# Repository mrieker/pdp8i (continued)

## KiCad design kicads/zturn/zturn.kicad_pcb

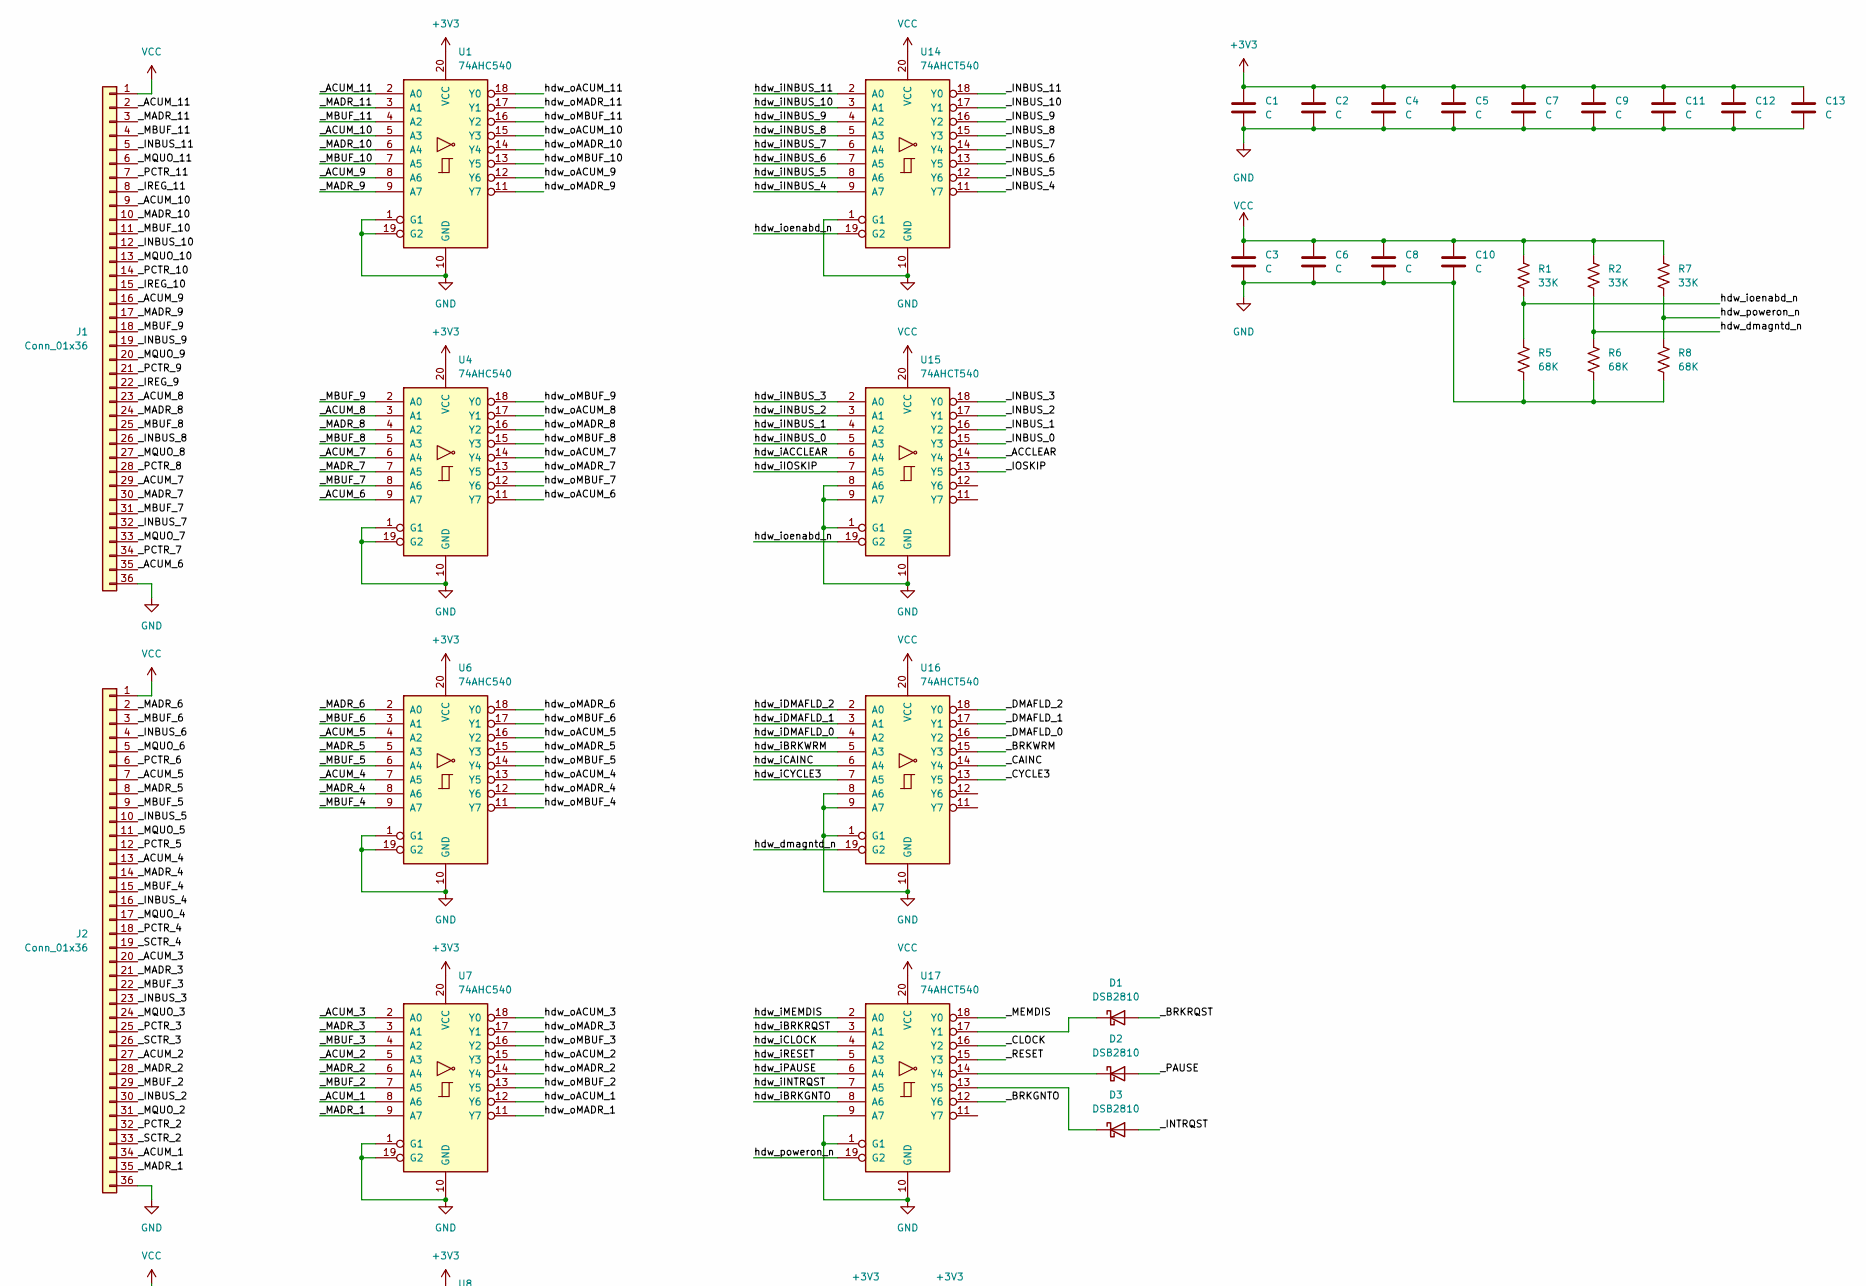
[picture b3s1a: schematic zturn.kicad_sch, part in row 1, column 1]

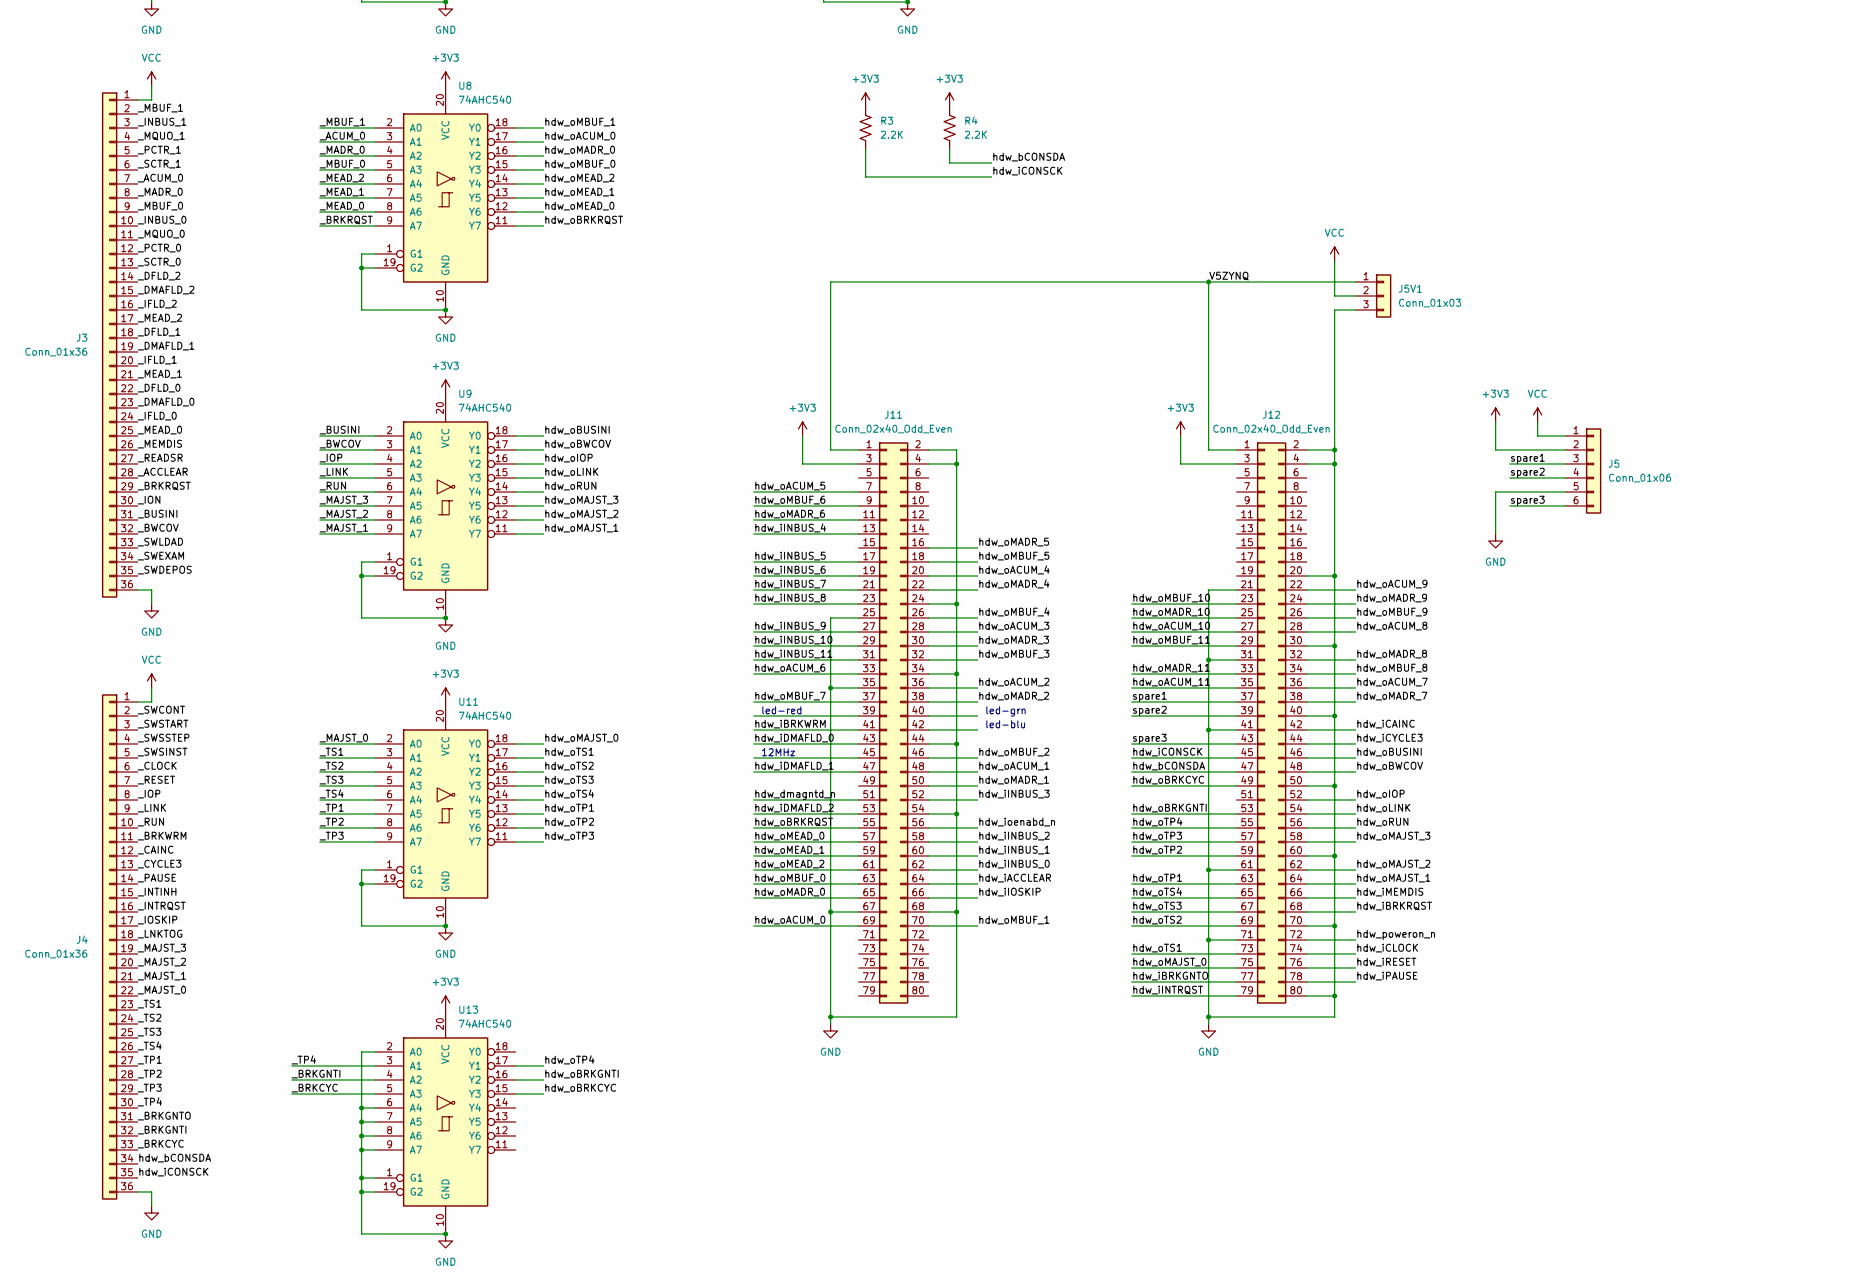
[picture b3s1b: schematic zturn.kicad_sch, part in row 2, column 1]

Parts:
C1, C2, C3, C4, C5, C6, C7, C8, C9, C10, C11, C12, C13: C; R_Axial_DIN0207_L6.3mm_D2.5mm_P7.62mm_Horizontal
D1, D2, D3: DSB2810; D_DO-35_SOD27_P7.62mm_Horizontal
J1, J2, J3, J4: Conn_01x36; PinHeader_1x36_P2.54mm_Vertical
J5: Conn_01x06; PinHeader_1x06_P2.54mm_Vertical
J5V1: Conn_01x03; PinHeader_1x03_P2.54mm_Horizontal
J11, J12: Conn_02x40_Odd_Even; PinHeader_2x40_P1.27mm_Vertical
R1, R2, R7: 33K; R_Axial_DIN0207_L6.3mm_D2.5mm_P7.62mm_Horizontal
R3, R4: 2.2K; R_Axial_DIN0207_L6.3mm_D2.5mm_P7.62mm_Horizontal
R5, R6, R8: 68K; R_Axial_DIN0207_L6.3mm_D2.5mm_P7.62mm_Horizontal
U1, U4, U6, U7, U8, U9, U11, U13: 74AHC540; DIP-20_W7.62mm
U14, U15, U16, U17: 74AHCT540; DIP-20_W7.62mm

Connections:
+3V3: C1.1, C2.1, C4.1, C5.1, C7.1, C9.1, C11.1, C12.1, C13.1, J5.2, J11.3, J12.3, R3.1, R4.1, U1.20 (VCC), U4.20 (VCC), U6.20 (VCC), U7.20 (VCC), U8.20 (VCC), U9.20 (VCC), U11.20 (VCC), U13.20 (VCC)
/V5ZYNQ: J5V1.1, J11.1, J12.1
/_ACCLEAR: J3.28, U15.14 (Y4)
/_ACUM_0: J3.7, U8.3 (A1)
/_ACUM_1: J2.34, U7.8 (A6)
/_ACUM_2: J2.27, U7.5 (A3)
/_ACUM_3: J2.20, U7.2 (A0)
/_ACUM_4: J2.13, U6.7 (A5)
/_ACUM_5: J2.7, U6.4 (A2)
/_ACUM_6: J1.35, U4.9 (A7)
/_ACUM_7: J1.29, U4.6 (A4)
/_ACUM_8: J1.23, U4.3 (A1)
/_ACUM_9: J1.16, U1.8 (A6)
/_ACUM_10: J1.9, U1.5 (A3)
/_ACUM_11: J1.2, U1.2 (A0)
/_BRKCYC: J4.33, U13.5 (A3)
/_BRKGNTI: J4.32, U13.4 (A2)
/_BRKGNTO: J4.31, U17.12 (Y6)
/_BRKRQST: D1.2 (A), J3.29, U8.9 (A7)
/_BRKWRM: J4.11, U16.15 (Y3)
/_BUSINI: J3.31, U9.2 (A0)
/_BWCOV: J3.32, U9.3 (A1)
/_CAINC: J4.12, U16.14 (Y4)
/_CLOCK: J4.6, U17.16 (Y2)
/_CYCLE3: J4.13, U16.13 (Y5)
/_DFLD_0: J3.22
/_DFLD_1: J3.18
/_DFLD_2: J3.14
/_DMAFLD_0: J3.23, U16.16 (Y2)
/_DMAFLD_1: J3.19, U16.17 (Y1)
/_DMAFLD_2: J3.15, U16.18 (Y0)
/_IFLD_0: J3.24
/_IFLD_1: J3.20
/_IFLD_2: J3.16
/_INBUS_0: J3.10, U15.15 (Y3)
/_INBUS_1: J3.3, U15.16 (Y2)
/_INBUS_2: J2.30, U15.17 (Y1)
/_INBUS_3: J2.23, U15.18 (Y0)
/_INBUS_4: J2.16, U14.11 (Y7)
/_INBUS_5: J2.10, U14.12 (Y6)
/_INBUS_6: J2.4, U14.13 (Y5)
/_INBUS_7: J1.32, U14.14 (Y4)
/_INBUS_8: J1.26, U14.15 (Y3)
/_INBUS_9: J1.19, U14.16 (Y2)
/_INBUS_10: J1.12, U14.17 (Y1)
/_INBUS_11: J1.5, U14.18 (Y0)
/_INTINH: J4.15
/_INTRQST: D3.2 (A), J4.16
/_ION: J3.30
/_IOP: J4.8, U9.4 (A2)
/_IOSKIP: J4.17, U15.13 (Y5)
/_IREG_9: J1.22
/_IREG_10: J1.15
/_IREG_11: J1.8
/_LINK: J4.9, U9.5 (A3)
/_LNKTOG: J4.18
/_MADR_0: J3.8, U8.4 (A2)
/_MADR_1: J2.35, U7.9 (A7)
/_MADR_2: J2.28, U7.6 (A4)
/_MADR_3: J2.21, U7.3 (A1)
/_MADR_4: J2.14, U6.8 (A6)
/_MADR_5: J2.8, U6.5 (A3)
/_MADR_6: J2.2, U6.2 (A0)
/_MADR_7: J1.30, U4.7 (A5)
/_MADR_8: J1.24, U4.4 (A2)
/_MADR_9: J1.17, U1.9 (A7)
/_MADR_10: J1.10, U1.6 (A4)
/_MADR_11: J1.3, U1.3 (A1)
/_MAJST_0: J4.22, U11.2 (A0)
/_MAJST_1: J4.21, U9.9 (A7)
/_MAJST_2: J4.20, U9.8 (A6)
/_MAJST_3: J4.19, U9.7 (A5)
/_MBUF_0: J3.9, U8.5 (A3)
/_MBUF_1: J3.2, U8.2 (A0)
/_MBUF_2: J2.29, U7.7 (A5)
/_MBUF_3: J2.22, U7.4 (A2)
/_MBUF_4: J2.15, U6.9 (A7)
/_MBUF_5: J2.9, U6.6 (A4)
/_MBUF_6: J2.3, U6.3 (A1)
/_MBUF_7: J1.31, U4.8 (A6)
/_MBUF_8: J1.25, U4.5 (A3)
/_MBUF_9: J1.18, U4.2 (A0)
/_MBUF_10: J1.11, U1.7 (A5)
/_MBUF_11: J1.4, U1.4 (A2)
/_MEAD_0: J3.25, U8.8 (A6)
/_MEAD_1: J3.21, U8.7 (A5)
/_MEAD_2: J3.17, U8.6 (A4)
/_MEMDIS: J3.26, U17.18 (Y0)
/_MQUO_0: J3.11
/_MQUO_1: J3.4
/_MQUO_2: J2.31
/_MQUO_3: J2.24
/_MQUO_4: J2.17
/_MQUO_5: J2.11
/_MQUO_6: J2.5
/_MQUO_7: J1.33
/_MQUO_8: J1.27
/_MQUO_9: J1.20
/_MQUO_10: J1.13
/_MQUO_11: J1.6
/_PAUSE: D2.2 (A), J4.14
/_PCTR_0: J3.12
/_PCTR_1: J3.5
/_PCTR_2: J2.32
/_PCTR_3: J2.25
/_PCTR_4: J2.18
/_PCTR_5: J2.12
/_PCTR_6: J2.6
/_PCTR_7: J1.34
/_PCTR_8: J1.28
/_PCTR_9: J1.21
/_PCTR_10: J1.14
/_PCTR_11: J1.7
/_READSR: J3.27
/_RESET: J4.7, U17.15 (Y3)
/_RUN: J4.10, U9.6 (A4)
/_SCTR_0: J3.13
/_SCTR_1: J3.6
/_SCTR_2: J2.33
/_SCTR_3: J2.26
/_SCTR_4: J2.19
/_SWCONT: J4.2
/_SWDEPOS: J3.35
/_SWEXAM: J3.34
/_SWLDAD: J3.33
/_SWSINST: J4.5
/_SWSSTEP: J4.4
/_SWSTART: J4.3
/_TP1: J4.27, U11.7 (A5)
/_TP2: J4.28, U11.8 (A6)
/_TP3: J4.29, U11.9 (A7)
/_TP4: J4.30, U13.3 (A1)
/_TS1: J4.23, U11.3 (A1)
/_TS2: J4.24, U11.4 (A2)
/_TS3: J4.25, U11.5 (A3)
/_TS4: J4.26, U11.6 (A4)
/hdw_bCONSDA: J4.34, J12.47, R4.2
/hdw_dmagntd_n: J11.51, R2.2, R6.2, U16.19 (G2)
/hdw_iACCLEAR: J11.64, U15.6 (A4)
/hdw_iBRKGNTO: J12.77, U17.8 (A6)
/hdw_iBRKRQST: J12.68, U17.3 (A1)
/hdw_iBRKWRM: J11.41, U16.5 (A3)
/hdw_iCAINC: J12.42, U16.6 (A4)
/hdw_iCLOCK: J12.74, U17.4 (A2)
/hdw_iCONSCK: J4.35, J12.45, R3.2
/hdw_iCYCLE3: J12.44, U16.7 (A5)
/hdw_iDMAFLD_0: J11.43, U16.4 (A2)
/hdw_iDMAFLD_1: J11.47, U16.3 (A1)
/hdw_iDMAFLD_2: J11.53, U16.2 (A0)
/hdw_iINBUS_0: J11.62, U15.5 (A3)
/hdw_iINBUS_1: J11.60, U15.4 (A2)
/hdw_iINBUS_2: J11.58, U15.3 (A1)
/hdw_iINBUS_3: J11.52, U15.2 (A0)
/hdw_iINBUS_4: J11.13, U14.9 (A7)
/hdw_iINBUS_5: J11.17, U14.8 (A6)
/hdw_iINBUS_6: J11.19, U14.7 (A5)
/hdw_iINBUS_7: J11.21, U14.6 (A4)
/hdw_iINBUS_8: J11.23, U14.5 (A3)
/hdw_iINBUS_9: J11.27, U14.4 (A2)
/hdw_iINBUS_10: J11.29, U14.3 (A1)
/hdw_iINBUS_11: J11.31, U14.2 (A0)
/hdw_iINTRQST: J12.79, U17.7 (A5)
/hdw_iIOSKIP: J11.66, U15.7 (A5)
/hdw_iMEMDIS: J12.66, U17.2 (A0)
/hdw_iPAUSE: J12.78, U17.6 (A4)
/hdw_iRESET: J12.76, U17.5 (A3)
/hdw_ioenabd_n: J11.56, R1.2, R5.2, U14.19 (G2), U15.19 (G2)
/hdw_oACUM_0: J11.69, U8.17 (Y1)
/hdw_oACUM_1: J11.48, U7.12 (Y6)
/hdw_oACUM_2: J11.36, U7.15 (Y3)
/hdw_oACUM_3: J11.28, U7.18 (Y0)
/hdw_oACUM_4: J11.20, U6.13 (Y5)
/hdw_oACUM_5: J11.7, U6.16 (Y2)
/hdw_oACUM_6: J11.33, U4.11 (Y7)
/hdw_oACUM_7: J12.36, U4.14 (Y4)
/hdw_oACUM_8: J12.28, U4.17 (Y1)
/hdw_oACUM_9: J12.22, U1.12 (Y6)
/hdw_oACUM_10: J12.27, U1.15 (Y3)
/hdw_oACUM_11: J12.35, U1.18 (Y0)
/hdw_oBRKCYC: J12.49, U13.15 (Y3)
/hdw_oBRKGNTI: J12.53, U13.16 (Y2)
/hdw_oBRKRQST: J11.55, U8.11 (Y7)
/hdw_oBUSINI: J12.46, U9.18 (Y0)
/hdw_oBWCOV: J12.48, U9.17 (Y1)
/hdw_oIOP: J12.52, U9.16 (Y2)
/hdw_oLINK: J12.54, U9.15 (Y3)
/hdw_oMADR_0: J11.65, U8.16 (Y2)
/hdw_oMADR_1: J11.50, U7.11 (Y7)
/hdw_oMADR_2: J11.38, U7.14 (Y4)
/hdw_oMADR_3: J11.30, U7.17 (Y1)
/hdw_oMADR_4: J11.22, U6.12 (Y6)
/hdw_oMADR_5: J11.16, U6.15 (Y3)
/hdw_oMADR_6: J11.11, U6.18 (Y0)
/hdw_oMADR_7: J12.38, U4.13 (Y5)
/hdw_oMADR_8: J12.32, U4.16 (Y2)
/hdw_oMADR_9: J12.24, U1.11 (Y7)
/hdw_oMADR_10: J12.25, U1.14 (Y4)
/hdw_oMADR_11: J12.33, U1.17 (Y1)
/hdw_oMAJST_0: J12.75, U11.18 (Y0)
/hdw_oMAJST_1: J12.64, U9.11 (Y7)
/hdw_oMAJST_2: J12.62, U9.12 (Y6)
/hdw_oMAJST_3: J12.58, U9.13 (Y5)
/hdw_oMBUF_0: J11.63, U8.15 (Y3)
/hdw_oMBUF_1: J11.70, U8.18 (Y0)
/hdw_oMBUF_2: J11.46, U7.13 (Y5)
/hdw_oMBUF_3: J11.32, U7.16 (Y2)
/hdw_oMBUF_4: J11.26, U6.11 (Y7)
/hdw_oMBUF_5: J11.18, U6.14 (Y4)
/hdw_oMBUF_6: J11.9, U6.17 (Y1)
/hdw_oMBUF_7: J11.37, U4.12 (Y6)
/hdw_oMBUF_8: J12.34, U4.15 (Y3)
/hdw_oMBUF_9: J12.26, U4.18 (Y0)
/hdw_oMBUF_10: J12.23, U1.13 (Y5)
/hdw_oMBUF_11: J12.29, U1.16 (Y2)
/hdw_oMEAD_0: J11.57, U8.12 (Y6)
/hdw_oMEAD_1: J11.59, U8.13 (Y5)
/hdw_oMEAD_2: J11.61, U8.14 (Y4)
/hdw_oRUN: J12.56, U9.14 (Y4)
/hdw_oTP1: J12.63, U11.13 (Y5)
/hdw_oTP2: J12.59, U11.12 (Y6)
/hdw_oTP3: J12.57, U11.11 (Y7)
/hdw_oTP4: J12.55, U13.17 (Y1)
/hdw_oTS1: J12.73, U11.17 (Y1)
/hdw_oTS2: J12.69, U11.16 (Y2)
/hdw_oTS3: J12.67, U11.15 (Y3)
/hdw_oTS4: J12.65, U11.14 (Y4)
/hdw_poweron_n: J12.72, R7.2, R8.2, U17.19 (G2)
/spare1: J5.3, J12.37
/spare2: J5.4, J12.39
/spare3: J5.6, J12.43
GND: C1.2, C2.2, C3.2, C4.2, C5.2, C6.2, C7.2, C8.2, C9.2, C10.2, C11.2, C12.2, C13.2, J1.36, J2.36, J3.36, J4.36, J5.5, J5V1.3, J11.2, J11.4, J11.24, J11.25, J11.34, J11.35, J11.44, J11.54, J11.67, J11.68, J12.2, J12.4, J12.20, J12.21, J12.30, J12.31, J12.40, J12.41, J12.50, J12.60, J12.61, J12.70, J12.71, J12.80, R5.1, R6.1, R8.1, U1.1 (G1), U1.10 (GND), U1.19 (G2), U4.1 (G1), U4.10 (GND), U4.19 (G2), U6.1 (G1), U6.10 (GND), U6.19 (G2), U7.1 (G1), U7.10 (GND), U7.19 (G2), U8.1 (G1), U8.10 (GND), U8.19 (G2), U9.1 (G1), U9.10 (GND), U9.19 (G2), U11.1 (G1), U11.10 (GND), U11.19 (G2), U13.1 (G1), U13.2 (A0), U13.6 (A4), U13.7 (A5), U13.8 (A6), U13.9 (A7), U13.10 (GND), U13.19 (G2), U14.1 (G1), U14.10 (GND), U15.1 (G1), U15.8 (A6), U15.9 (A7), U15.10 (GND), U16.1 (G1), U16.8 (A6), U16.9 (A7), U16.10 (GND), U17.1 (G1), U17.9 (A7), U17.10 (GND)
unnamed: D1.1 (K), U17.17 (Y1)
unnamed: D2.1 (K), U17.14 (Y4)
unnamed: D3.1 (K), U17.13 (Y5)
VCC: C3.1, C6.1, C8.1, C10.1, J1.1, J2.1, J3.1, J4.1, J5.1, J5V1.2, R1.1, R2.1, R7.1, U14.20 (VCC), U15.20 (VCC), U16.20 (VCC), U17.20 (VCC)

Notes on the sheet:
led-red
led-blu
12MHz
led-grn

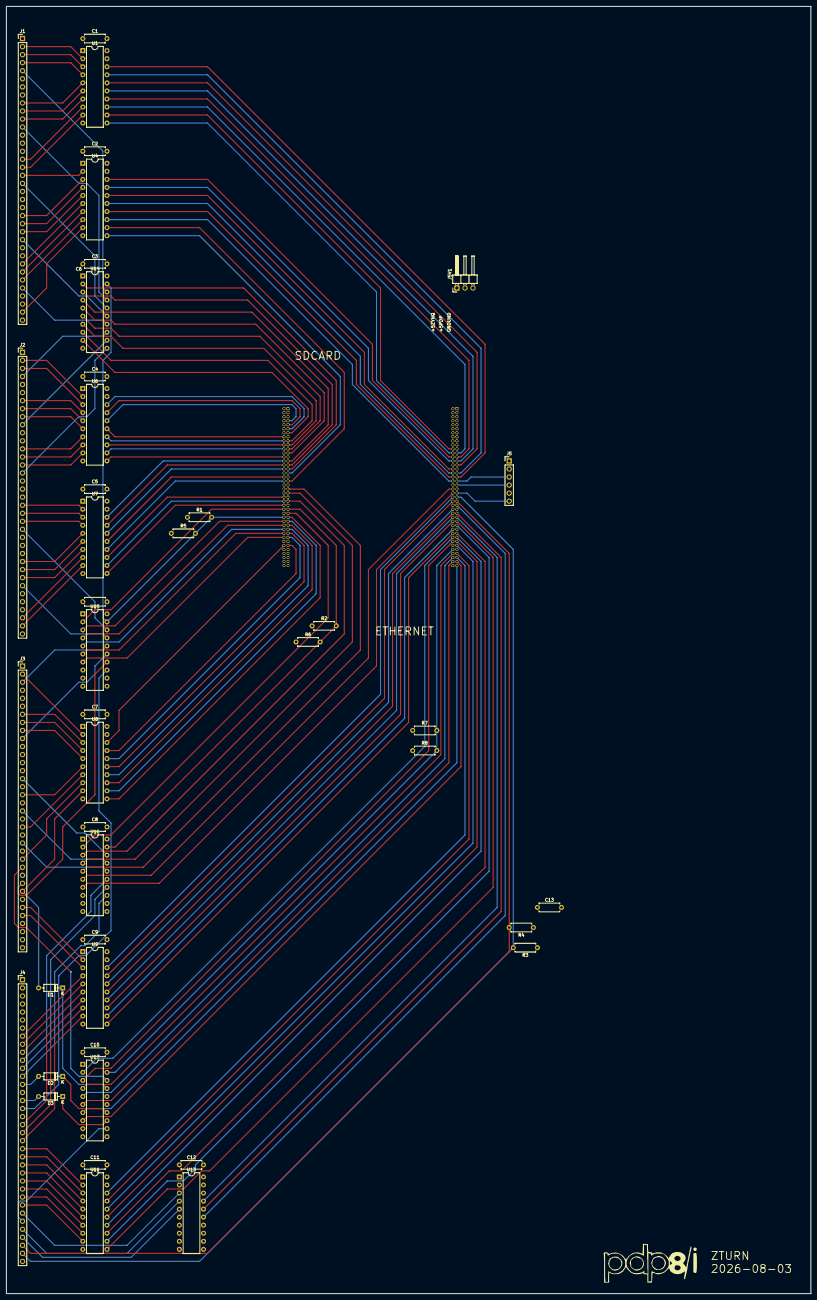
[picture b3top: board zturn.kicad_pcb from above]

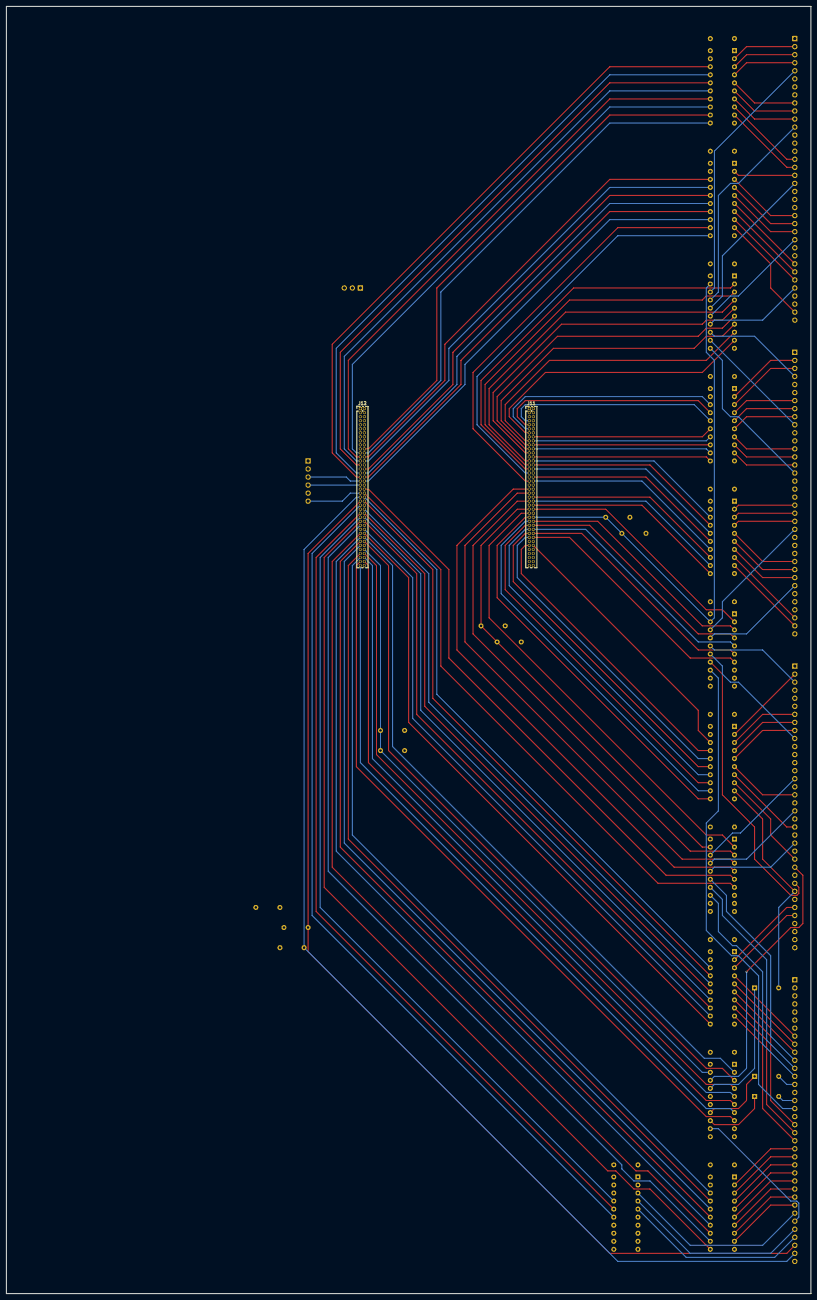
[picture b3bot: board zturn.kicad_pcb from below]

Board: 4 copper layers, 254.0 x 406.4 mm, 44 parts (2 on the bottom side), 186 nets.
